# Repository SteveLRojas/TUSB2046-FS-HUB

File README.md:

# TUSB2046-FS-HUB
USB full speed hub with probe points for USB development use.

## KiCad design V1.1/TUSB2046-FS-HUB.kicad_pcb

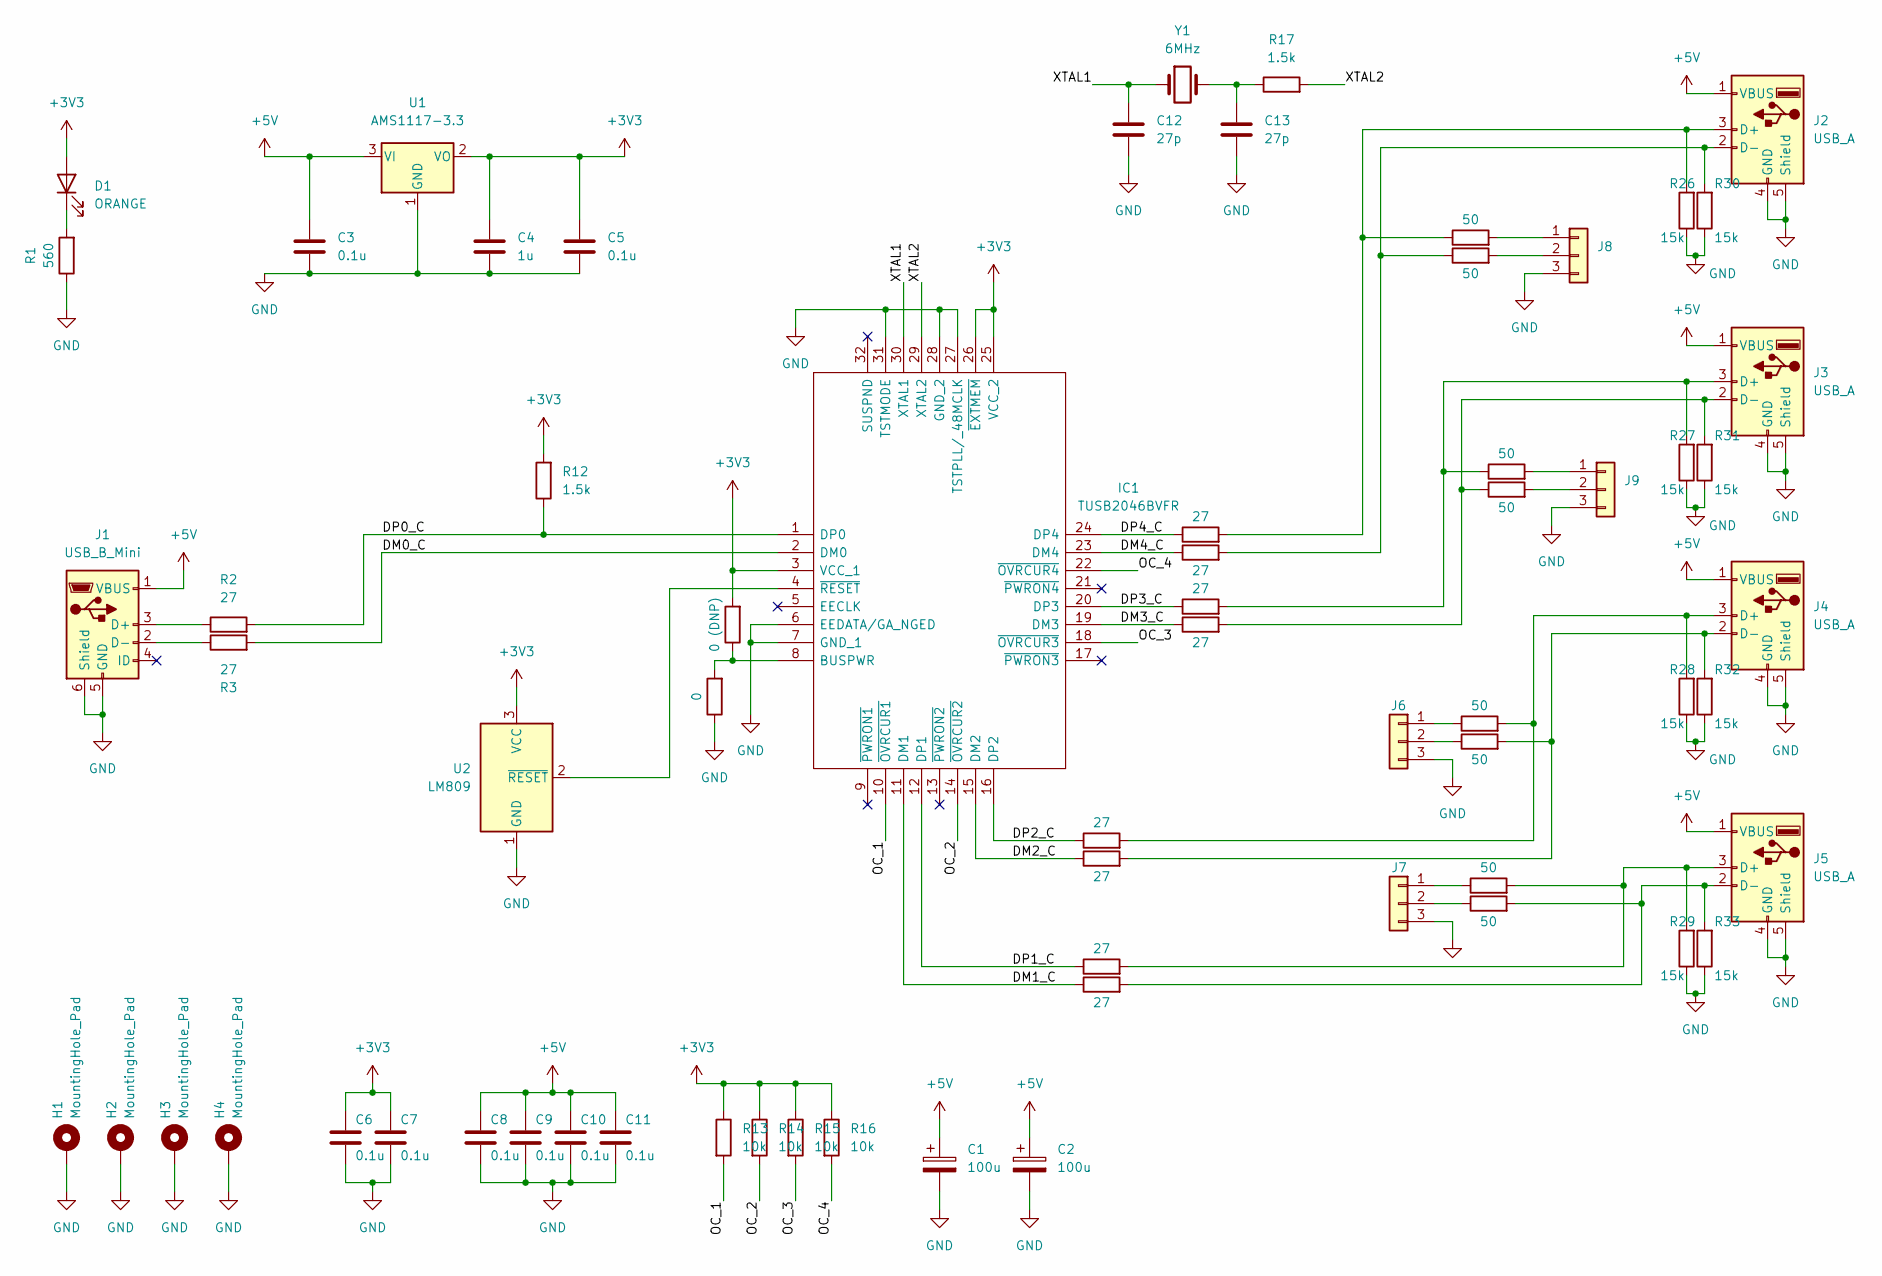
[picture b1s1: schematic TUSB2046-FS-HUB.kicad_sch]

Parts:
C1, C2: 100u; CP_Elec_6.3x5.2
C3, C5, C6, C7, C8, C9, C10, C11: 0.1u; C_0805_2012Metric
C4: 1u; C_0805_2012Metric
C12, C13: 27p; C_0805_2012Metric
D1: ORANGE; LED_0805_2012Metric
H1, H2, H3, H4: MountingHole_Pad; MountingHole_3.2mm_M3_Pad
IC1: TUSB2046BVFR; QFP80P900X900X160-32N; Mouser Part Number 595-TUSB2046BVFR
J1: USB_B_Mini; USB_Mini-B_Wuerth_65100516121_Horizontal
J2, J3, J4, J5: USB_A; USB_A_CONNFLY_DS1095-WNR0
J6, J7, J8, J9: Conn_01x03; PinHeader_1x03_P2.54mm_Vertical
R1: 560; R_0805_2012Metric
R2, R3, R4, R5, R6, R7, R8, R9, R10, R11: 27; R_0805_2012Metric
R12, R17: 1.5k; R_0805_2012Metric
R13, R14, R15, R16: 10k; R_0805_2012Metric
R18, R19, R20, R21, R22, R23, R24, R25: 50; R_0805_2012Metric
R26, R27, R28, R29, R30, R31, R32, R33: 15k; R_0805_2012Metric
R34: 0; R_0805_2012Metric
R35: 0 (DNP); R_0805_2012Metric
U1: AMS1117-3.3; SOT-223-3_TabPin2
U2: LM809; SOT-23
Y1: 6MHz; Crystal_HC49-4H_Vertical

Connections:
+3V3: C4.1, C5.1, C6.1, C7.1, D1.2 (A), IC1.3 (VCC_1), IC1.25 (VCC_2), IC1.26 (~EXTMEM), R12.2, R13.1, R14.1, R15.1, R16.1, R35.2, U1.2 (VO), U2.3 (VCC)
+5V: C1.1, C2.1, C3.1, C8.1, C9.1, C10.1, C11.1, J1.1 (VBUS), J2.1 (VBUS), J3.1 (VBUS), J4.1 (VBUS), J5.1 (VBUS), U1.3 (VI)
/DM0_C: IC1.2 (DM0), R3.2
/DM1_C: IC1.11 (DM1), R7.1
/DM2_C: IC1.15 (DM2), R5.1
/DM3_C: IC1.19 (DM3), R11.1
/DM4_C: IC1.23 (DM4), R9.1
/DP0_C: IC1.1 (DP0), R2.2, R12.1
/DP1_C: IC1.12 (DP1), R6.1
/DP2_C: IC1.16 (DP2), R4.1
/DP3_C: IC1.20 (DP3), R10.1
/DP4_C: IC1.24 (DP4), R8.1
/OC_1: IC1.10 (~OVRCUR1), R13.2
/OC_2: IC1.14 (~OVRCUR2), R14.2
/OC_3: IC1.18 (~OVRCUR3), R15.2
/OC_4: IC1.22 (~OVRCUR4), R16.2
/XTAL1: C12.1, IC1.30 (XTAL1), Y1.1
/XTAL2: IC1.29 (XTAL2), R17.2
GND: C1.2, C2.2, C3.2, C4.2, C5.2, C6.2, C7.2, C8.2, C9.2, C10.2, C11.2, C12.2, C13.2, H1.1, H2.1, H3.1, H4.1, IC1.6 (EEDATA/GA_NGED), IC1.7 (GND_1), IC1.27 (TSTPLL/_48MCLK), IC1.28 (GND_2), IC1.31 (TSTMODE), J1.5 (GND), J1.6 (Shield), J2.4 (GND), J2.5 (Shield), J3.4 (GND), J3.5 (Shield), J4.4 (GND), J4.5 (Shield), J5.4 (GND), J5.5 (Shield), J6.3, J7.3, J8.3, J9.3, R1.1, R26.1, R27.1, R28.1, R29.1, R30.1, R31.1, R32.1, R33.1, R34.1, U1.1 (GND), U2.1 (GND)
unnamed: C13.1, R17.1, Y1.2
unnamed: D1.1 (K), R1.2
unnamed: IC1.4 (~RESET), U2.2 (~RESET)
unnamed: IC1.8 (BUSPWR), R34.2, R35.1
unnamed: J1.2 (D-), R3.1
unnamed: J1.3 (D+), R2.1
unnamed: J2.2 (D-), R9.2, R19.1, R30.2
unnamed: J2.3 (D+), R8.2, R18.1, R26.2
unnamed: J3.2 (D-), R11.2, R25.1, R31.2
unnamed: J3.3 (D+), R10.2, R24.1, R27.2
unnamed: J4.2 (D-), R5.2, R21.2, R32.2
unnamed: J4.3 (D+), R4.2, R20.2, R28.2
unnamed: J5.2 (D-), R7.2, R23.2, R33.2
unnamed: J5.3 (D+), R6.2, R22.2, R29.2
unnamed: J6.1, R20.1
unnamed: J6.2, R21.1
unnamed: J7.1, R22.1
unnamed: J7.2, R23.1
unnamed: J8.1, R18.2
unnamed: J8.2, R19.2
unnamed: J9.1, R24.2
unnamed: J9.2, R25.2

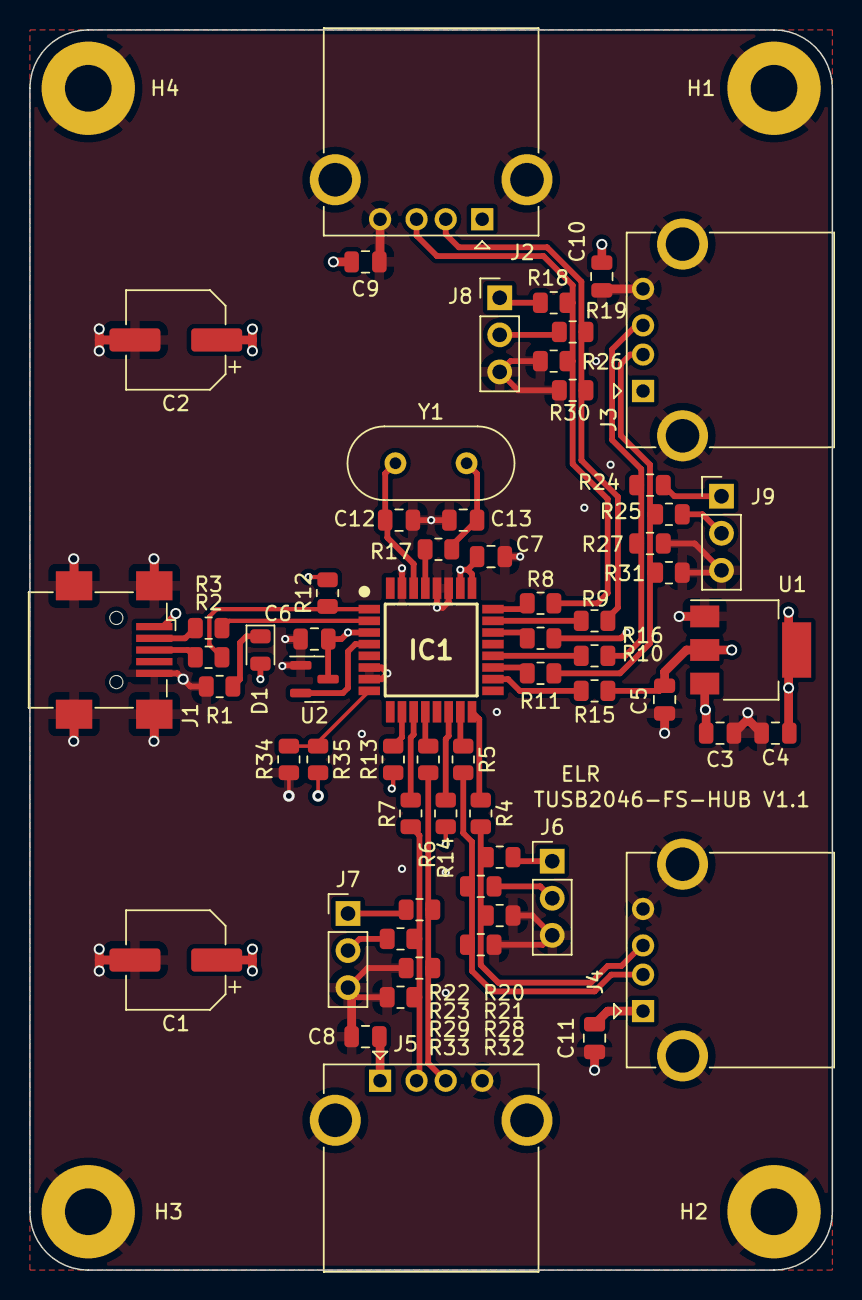
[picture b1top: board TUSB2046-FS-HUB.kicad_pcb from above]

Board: 4 copper layers, 55.0 x 85.0 mm, 66 parts (0 on the bottom side), 41 nets.

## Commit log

2024-04-26 Added V1.0 files
2024-04-26 Added render and layout PDFs
2024-04-30 Created V1.1 (power source select)
2024-05-10 Adjusted LED brightness
